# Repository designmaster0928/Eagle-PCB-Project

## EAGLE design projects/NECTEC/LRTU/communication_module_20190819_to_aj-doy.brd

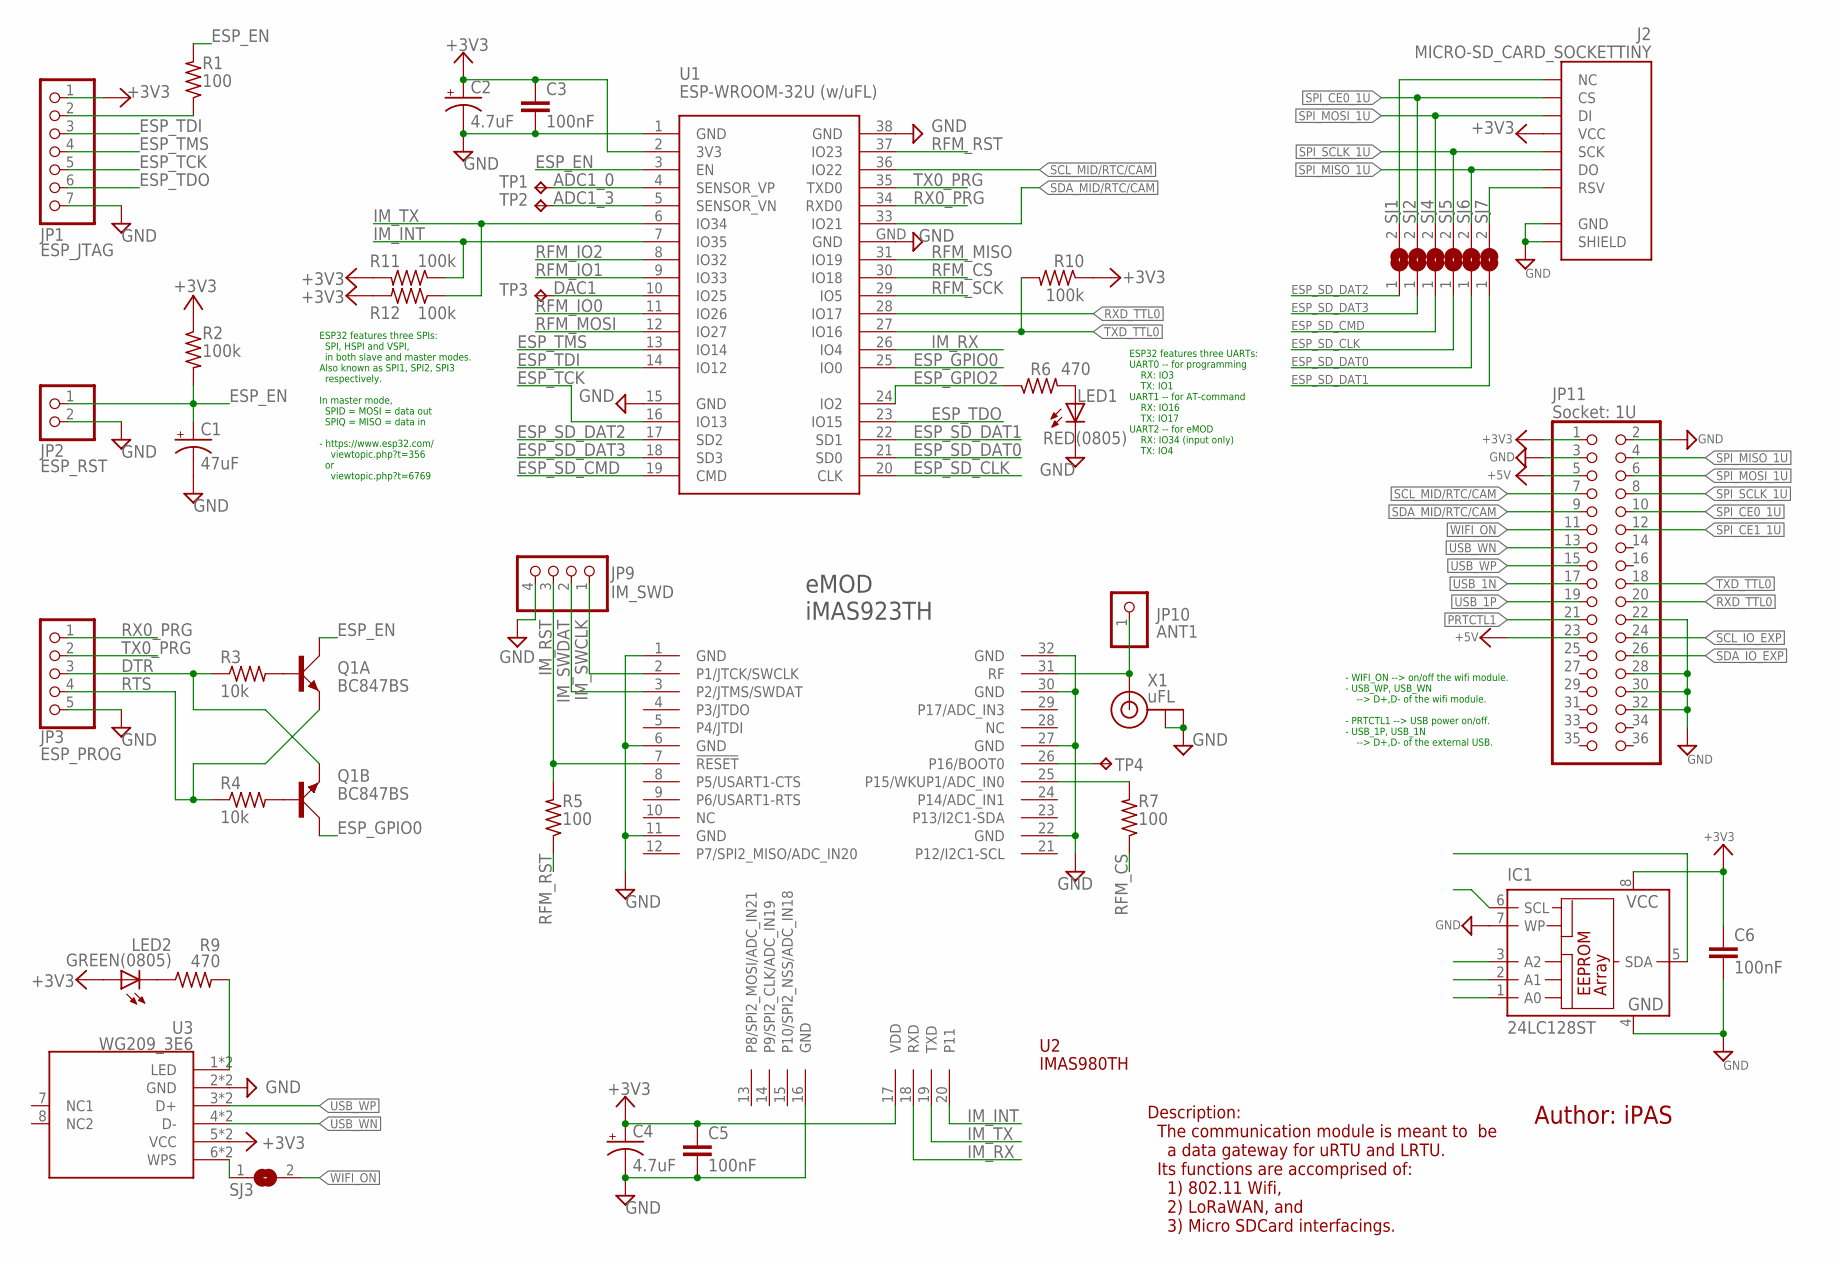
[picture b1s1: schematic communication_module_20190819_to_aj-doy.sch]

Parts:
C1: 47uF; RCL_150CLZ-1014
C2, C4: 4.7uF; RCL_150CLZ-1014
C3, C5, C6: 100nF; RCL_C1206
IC1: 24LC128ST; TSSOP8
J2: MICRO-SD_CARD_SOCKETTINY; MICROSD_TINY
JP1: ESP_JTAG; 1X07
JP2: ESP_RST; 1X02
JP3: ESP_PROG; 1X05
JP9: IM_SWD; 1X04
JP10: ANT1; 1X01_ROUND
JP11: Socket: 1U; 2X18
LED1: RED(0805); CHIP-LED0805
LED2: GREEN(0805); CHIP-LED0805
Q1: BC847BS; SOT363_PHILIPS
R1, R5, R7: 100; RCL_M0805
R2, R10, R11, R12: 100k; RCL_M0805
R3, R4: 10k; RCL_M0805
R6, R9: 470; RCL_M0805
SJ1, SJ2, SJ3, SJ4, SJ5, SJ6, SJ7: SOLDERJUMPERREFLOW; SOLDERJUMPER_REFLOW
TP1, TP2, TP3, TP4: TPB1,27; B1,27
U1: ESP-WROOM-32U (w/uFL); ESP-WROOM-32
U2: IMAS980TH; IMAS923TH
U3: WG209_3E6; WG209
X1: uFL; U.FL

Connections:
+3V3: C2.+, C3.1, C4.+, C5.1, C6.1, IC1.8 (VCC), J2.4 (VCC), JP1.1, JP11.1, LED2.A, R2.1, R10.1, R11.2, R12.2, U1.2 (3V3), U2.17 (VDD), U3.5 (VCC), U3.5P (VCC)
+5V: JP11.5, JP11.23
ADC1_0: TP1.TP, U1.4 (SENSOR_VP)
ADC1_3: TP2.TP, U1.5 (SENSOR_VN)
DAC1: TP3.TP, U1.10 (IO25)
DTR: JP3.3, Q1.4 (E), R3.1
ESP_EN: C1.+, JP2.1, Q1.6 (C), R1.2, R2.2, U1.3 (EN)
ESP_GPIO0: Q1.3 (C), U1.25 (IO0)
ESP_GPIO2: R6.1, U1.24 (IO2)
ESP_SD_CLK: SJ5.1, U1.20 (CLK)
ESP_SD_CMD: SJ4.1, U1.19 (CMD)
ESP_SD_DAT0: SJ6.1, U1.21 (SD0)
ESP_SD_DAT1: SJ7.1, U1.22 (SD1)
ESP_SD_DAT2: SJ1.1, U1.17 (SD2)
ESP_SD_DAT3: SJ2.1, U1.18 (SD3)
ESP_TCK: JP1.5, U1.16 (IO13)
ESP_TDI: JP1.3, U1.14 (IO12)
ESP_TDO: JP1.6, U1.23 (IO15)
ESP_TMS: JP1.4, U1.13 (IO14)
GND: C1.-, C2.-, C3.2, C4.-, C5.2, C6.2, IC1.4 (GND), IC1.7 (WP), J2.6 (GND), J2.GND1 (SHIELD), J2.GND2 (SHIELD), J2.GND3 (SHIELD), J2.GND4 (SHIELD), J2.GND5 (SHIELD), J2.GND6 (SHIELD), JP1.7, JP2.2, JP3.5, JP9.4, JP11.2, JP11.3, JP11.22, JP11.28, JP11.30, JP11.32, LED1.C, U1.1 (GND), U1.15 (GND), U1.38 (GND), U1.GND, U2.1 (GND), U2.6 (GND), U2.11 (GND), U2.16 (GND), U2.22 (GND), U2.27 (GND), U2.30 (GND), U2.32 (GND), U3.2 (GND), U3.2P (GND), X1.1 (GND), X1.2 (GND)
IM_INT: R11.1, U1.7 (IO35), U2.20 (P11)
IM_RST: JP9.3, R5.2, U2.7 (!RESET)
IM_RX: U1.26 (IO4), U2.18 (RXD)
IM_SWCLK: JP9.1, U2.2 (P1/JTCK/SWCLK)
IM_SWDAT: JP9.2, U2.3 (P2/JTMS/SWDAT)
IM_TX: R12.1, U1.6 (IO34), U2.19 (TXD)
unnamed: R9.2, U3.1 (LED), U3.1P (LED)
unnamed: SJ3.1, U3.6 (WPS), U3.6P (WPS)
unnamed: LED2.C, R9.1
unnamed: TP4.TP, U2.26 (P16/BOOT0)
unnamed: R7.2, U2.25 (P15/WKUP1/ADC_IN0)
unnamed: LED1.A, R6.2
unnamed: J2.9 (NC), SJ1.2
unnamed: J2.1 (RSV), J2.8 (RSV), SJ7.2
unnamed: JP10.1, U2.31 (RF), X1.3 (SIGNAL)
unnamed: Q1.2 (B), R3.2
unnamed: Q1.5 (B), R4.2
unnamed: JP1.2, R1.1
PRTCTL1: JP11.21
RFM_CS: R7.1, U1.30 (IO18)
RFM_IO0: U1.11 (IO26)
RFM_IO1: U1.9 (IO33)
RFM_IO2: U1.8 (IO32)
RFM_MISO: U1.31 (IO19)
RFM_MOSI: U1.12 (IO27)
RFM_RST: R5.1, U1.37 (IO23)
RFM_SCK: U1.29 (IO5)
RTS: JP3.4, Q1.1 (E), R4.1
RX0_PRG: JP3.1, U1.34 (RXD0)
RXD_TTL0: JP11.20, U1.28 (IO17)
SCL_IO_EXP: JP11.24
SCL_MID/RTC/CAM: JP11.7, U1.36 (IO22)
SDA_IO_EXP: JP11.26
SDA_MID/RTC/CAM: JP11.9, U1.33 (IO21)
SPI_CE0_1U: J2.2 (CS), JP11.10, SJ2.2
SPI_CE1_1U: JP11.12
SPI_MISO_1U: J2.7 (DO), JP11.4, SJ6.2
SPI_MOSI_1U: J2.3 (DI), JP11.6, SJ4.2
SPI_SCLK_1U: J2.5 (SCK), JP11.8, SJ5.2
TX0_PRG: JP3.2, U1.35 (TXD0)
TXD_TTL0: JP11.18, R10.2, U1.27 (IO16)
USB_1N: JP11.17
USB_1P: JP11.19
USB_WN: JP11.13, U3.4 (D-), U3.4P (D-)
USB_WP: JP11.15, U3.3 (D+), U3.3P (D+)
WIFI_ON: JP11.11, SJ3.2

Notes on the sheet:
ESP32 features three SPIs: SPI, HSPI and VSPI, in both slave and master modes. Also known as SPI1, SPI2, SPI3 respectively. In master mode, SPID = MOSI = data out SPIQ = MISO = data in - https://www.esp32.com/ viewtopic.php?t=356 or viewtopic.php?t=6769
- WIFI_ON --> on/off the wifi module. - USB_WP, USB_WN --> D+,D- of the wifi module. - PRTCTL1 --> USB power on/off. - USB_1P, USB_1N --> D+,D- of the external USB.
Description: The communication module is meant to be a data gateway for uRTU and LRTU. Its functions are accomprised of: 1) 802.11 Wifi, 2) LoRaWAN, and 3) Micro SDCard interfacings.
Author: iPAS
ESP32 features three UARTs: UART0 -- for programming RX: IO3 TX: IO1 UART1 -- for AT-command RX: IO16 TX: IO17 UART2 -- for eMOD RX: IO34 (input only) TX: IO4

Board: 2 copper layers, 43 parts (0 on the bottom side), 54 nets, no tracks yet.

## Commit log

2023-08-13 work-8.12

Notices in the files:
parts and their libraries:
microbuilder: This work is placed in the public domain, and may be freely used for commercial and non-commercial work with the following conditions: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
esp32: Creative Commons Attribution-ShareAlike 4.0 International
